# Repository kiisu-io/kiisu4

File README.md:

# Kiisu V4 docs, schematics and resources

## Kiisu V4b

[User Manual and Quick Start guide](https://github.com/kiisu-io/kiisu4/blob/main/kiisu%20v4b%20manual%20and%20quick%20start.pdf)

[Schematics](https://github.com/kiisu-io/kiisu4/blob/main/kiisu%20v4b%20schematics.pdf)

[STL file of board](https://github.com/kiisu-io/kiisu4/blob/main/kiisu%20v4b%20model.stl)

## Kiisu V4a

[User Manual for Kiisu v4a](https://github.com/kiisu-io/kiisu4/blob/main/previous/kiisu%20v4a%20manual.pdf)

[Schematics for Kiisu v4a](https://github.com/kiisu-io/kiisu4/blob/main/previous/kiisu%20v4a%20schematics.pdf)

## Check other resources:
- [Kiisu.io website](https://kiisu.io).
- [Buy Kiisu here](https://store.rainwalker.ee/products/kiisu-v4).
- [Our Discord Community](https://discord.gg/kiisu) can help with your questions.
- [Flipper Zero docs](https://docs.flipper.net/) to know more about Bluetooth, RFID, NFC, IR and other technologies and how to interact with it using compatible firmware on Kiisu board.

- [Aux MCU firmware to support Flipper Zero firmwares](https://github.com/kiisu-io/kiisu4-companion-fw).
- [Fork of Flipper Zero firmware for Kiisu](https://github.com/kiisu-io/kiisu-firmware).
- [Twoelw's GitHub](https://github.com/twoelw) with useful apps and firmware for Kiisu.

- [Cases and stuff for 3D printing on Printables](https://www.printables.com/@planmarks/collections/2364779).
- [Cases and stuff for 3D printing on Makerworld](https://makerworld.com/ru/collections/6517412-kiisu-devboard).

## See also

- [KIISU SMOL](https://github.com/kiisu-io/kiisu-smol) — hardware design files for our modular networking development board (currently on [Indiegogo](https://www.indiegogo.com/projects/rainwalker/kiisu-smol---networking-development-board)).

## License

Hardware design files (schematics, 3D models) are released under the [CERN Open Hardware Licence Version 2 — Strongly Reciprocal (CERN-OHL-S v2)](LICENSE).

The hardware design is open only to the extent published in this repository. Schematics are provided as PDF documents and the boards as 3D models; the original CAD sources (schematic and PCB layout projects) of Kiisu V4 boards are not published, are not part of the licensed material and are not available on request.

Documentation, manuals, and this README are released under the [Creative Commons Attribution-ShareAlike 4.0 International (CC BY-SA 4.0)](LICENSE-DOCS).

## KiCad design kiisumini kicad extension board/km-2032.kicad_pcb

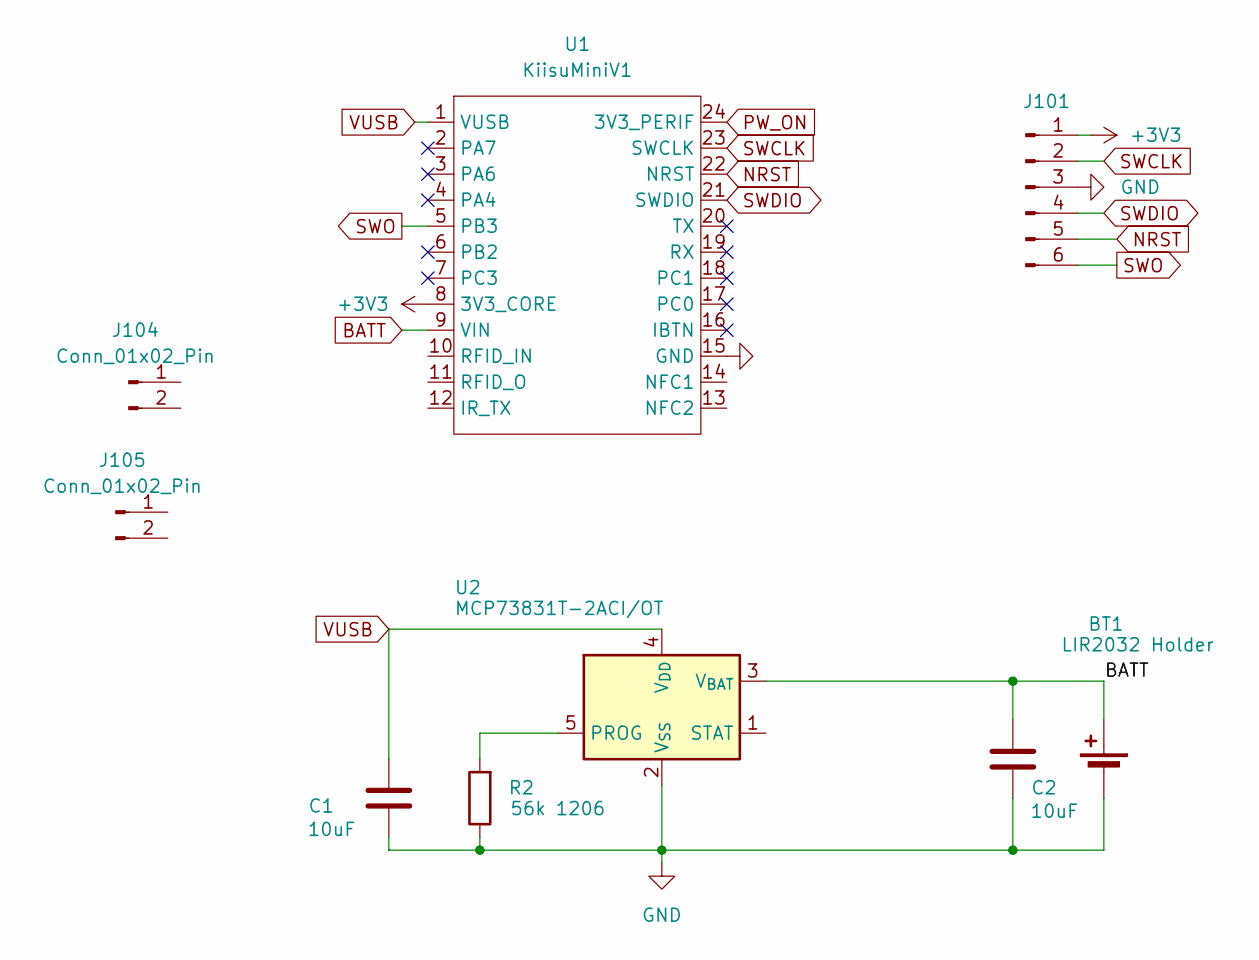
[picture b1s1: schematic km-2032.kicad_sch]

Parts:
BT1: MY-2032-12; CR2032-3
C1, C2: 10uF; C_0603_1608Metric
J101: ZX-PZ1.0-1-4PZZ; PinHeader_1x06_P1.00 press
J104: Conn_01x02_Pin; JST_XH_S2B-XH-A_1x02_P2.50mm_Horizontal
J105: Conn_01x02_Pin; JST_PH_S2B-PH-K_1x02_P2.00mm_Horizontal
R2: 56k 1206; R_1206_3216Metric
U1: KiisuMiniV1
U2: MCP73831T-2ACI/OT; SOT-23-5

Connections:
+3V3: J101.1, U1.8 (3V3_CORE)
BATT: BT1.+, C2.1, U1.9 (VIN), U2.3 (V_{BAT})
GND: BT1.-, C1.1, C2.2, J101.3, R2.1, U1.15 (GND), U2.2 (V_{SS})
NRST: J101.5, U1.22 (NRST)
unnamed: R2.2, U2.5 (PROG)
PW_ON: U1.24 (3V3_PERIF)
SWCLK: J101.2, U1.23 (SWCLK)
SWDIO: J101.4, U1.21 (SWDIO)
SWO: J101.6, U1.5 (PB3)
VUSB: C1.2, U1.1 (VUSB), U2.4 (V_{DD})

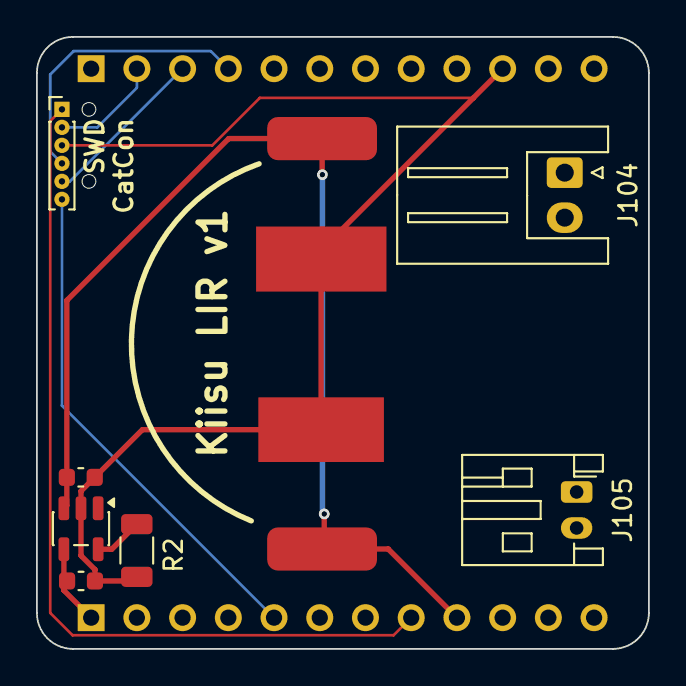
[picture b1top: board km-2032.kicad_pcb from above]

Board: 2 copper layers, 34.0 x 34.0 mm, 9 parts (0 on the bottom side), 9 nets.

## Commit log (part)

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2025-05-29 Schematics v4a.
2025-05-29 v4a manual
2025-08-13 v4b schematics and 3d models
2025-10-10 V4B updated manual
2025-10-11 Quick start guide and manual update.
2025-10-11 manual update
2026-01-02 Added info about NFC antenna tuning.
2026-02-11 Kiisu v4 in GLB format
2026-02-11 kiisumini v1a schematics and models
2026-02-11 kiisumini v1a expansion board sample project and footprints
2026-04-28 Migrate KIISU SMOL files to dedicated kiisu-smol repo, add licenses
    - Move kiisumini v1a hardware files (formerly the legacy name for KIISU SMOL)
    to https://github.com/kiisu-io/kiisu-smol
    - Add LICENSE: CERN-OHL-S v2 (hardware design files)
    - Add LICENSE-DOCS: CC-BY-SA 4.0 (documentation, manuals, README)
    - README: add "See also" pointer to kiisu-smol and a License section
